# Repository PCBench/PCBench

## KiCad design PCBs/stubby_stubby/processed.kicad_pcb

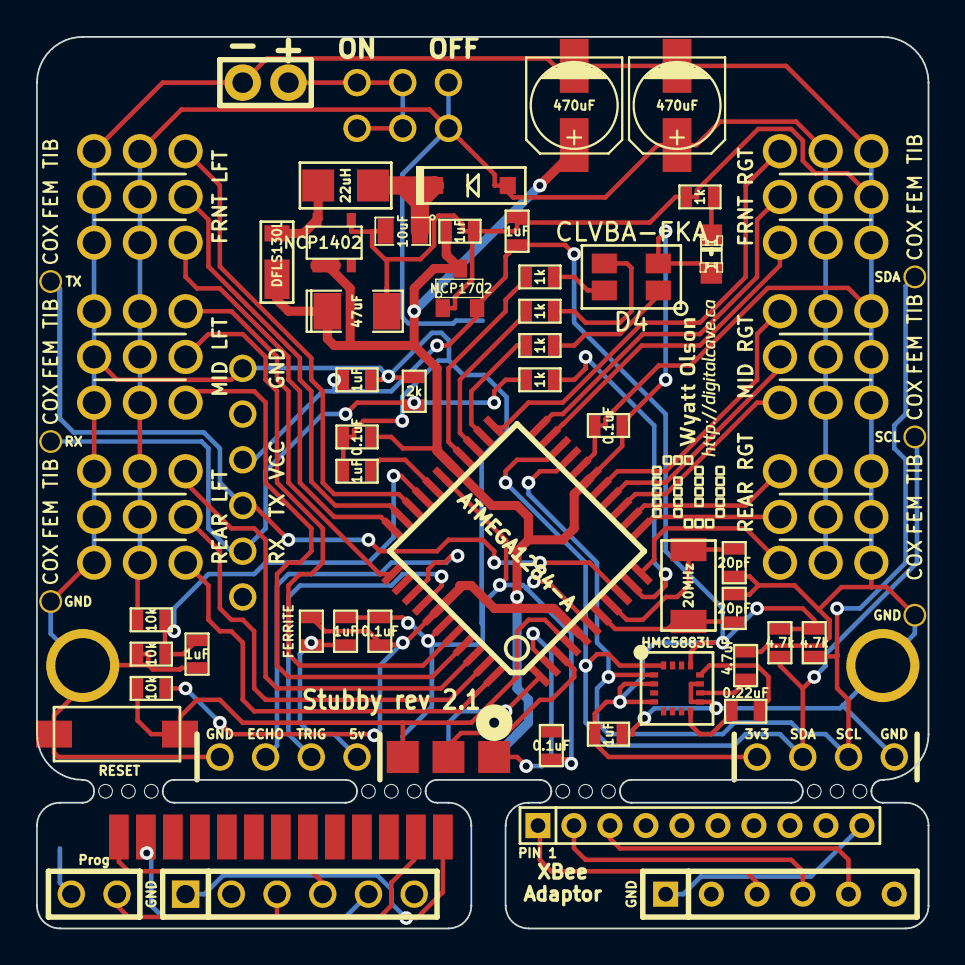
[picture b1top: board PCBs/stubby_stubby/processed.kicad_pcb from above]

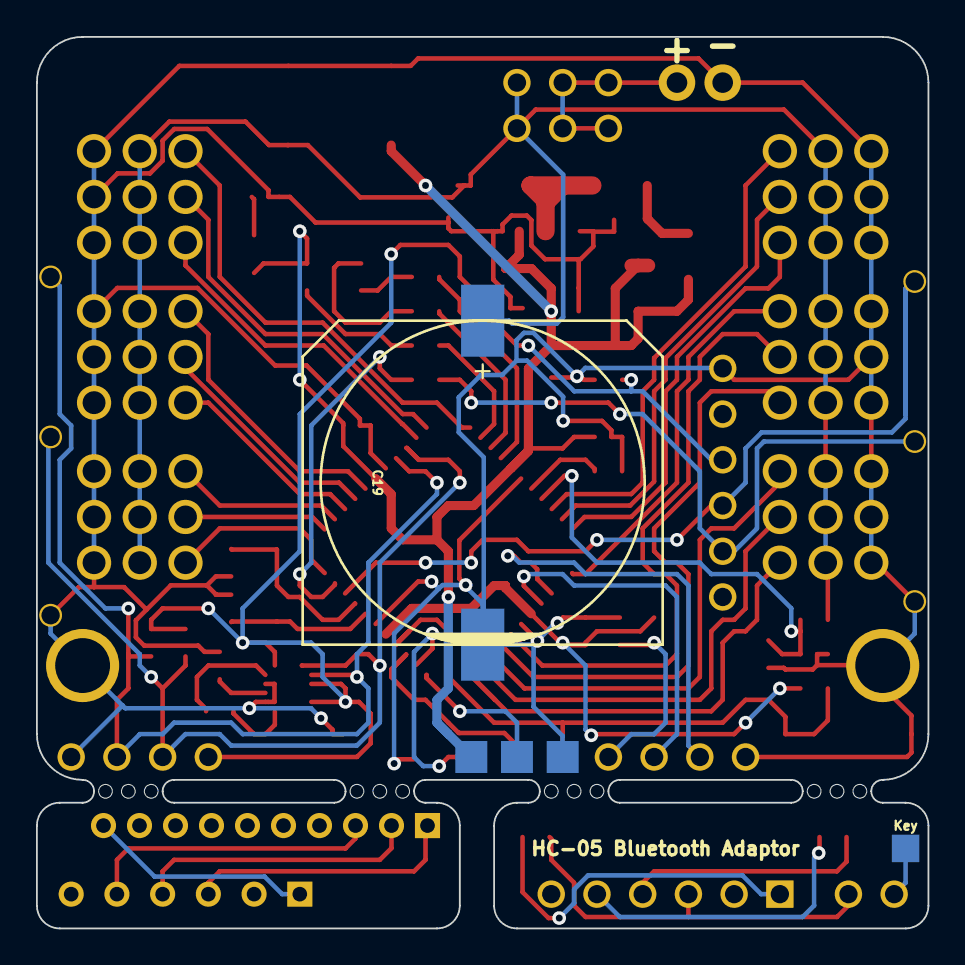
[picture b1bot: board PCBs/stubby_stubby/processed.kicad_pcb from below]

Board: 2 copper layers, 49.5 x 49.5 mm, 74 parts (2 on the bottom side), 60 nets.

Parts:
1PIN, 1PIN_2, 1PIN_3, 1PIN_4, 1PIN_5, 1PIN_6, 1PIN_7, 1PIN_8: P***; 1pin
C1: 10uF; SM0805
C2, C3, C6, C15, C16, C17, C18: 1uF; SM0603_VALUE
C4: 47uF; SM1206POL
C5, C20: 470uF; c_elec_5x5.3
C7: 4.7uF; SM0603_VALUE
C8, C9: 20pF; SM0603_VALUE
C10: 0.22uF; SM0603_VALUE
C11, C12, C13, C14: 0.1uF; SM0603_VALUE
C19: 6800µF; c_elec_18x18
D1: 1N4148W; SOD-123_DIODE
D2: DFLS130L; POWERDI_123
D3: LED; LED-0805-MARKED_ANODE
D4: CLVBA-FKA; 4-PLCC
IC1: ATMEGA1284-A; TQFP44
L1: 22uH; SM1007
L2: FERRITE; SM0603_VALUE
P1, P6, P11: CONN_6; SIL-6
P2, P10: CONN_4; SIL-4
P3: CONN_13; HC05_Edge
P4: CONN_2; SIL-2
P5: CONN_1; SIL-1
P7: CONN_10; SIL-10
P8: BATT (4.8V-6V); SIL-2
P9: PROG; ISP_EDGE
R1, R2: 4.7k; SM0603_VALUE
R3, R5, R6: 10k; SM0603_VALUE
R4, R7, R9, R10, R11: 1k; SM0603_VALUE
R8: 2k; SM0603_VALUE
S1: FRNT LFT; HEX_LEG
S2: FRNT RGT; HEX_LEG_REVERSE
S3: MID LFT; HEX_LEG
S4: MID RGT; HEX_LEG_REVERSE
S5: REAR LFT; HEX_LEG
S6: REAR RGT; HEX_LEG_REVERSE
SW1: SW_PUSH; SW_6x3
SW2: DPDT
U1: HMC5883L; LPCC-16
VAL: DIGITALCAVE_LOGO_WIDE_SMALL
VR1: MCP1702; SOT23
VR2: NCP1402; SOT23-5
X1: 20MHz; CRYSTAL_SMD_5x3.2
mouse_bites: VAL**; mouse_bites
mouse_bites_2, mouse_bites_3, mouse_bites_4: VAL**; mouse_bites

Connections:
+3.3V: C2.1, C15.1, C18.2, P2.1, P11.3, R1.2, R2.2, U1.2, U1.4, U1.13, VR1.3
+5V: C3.1, C4.1, C5.1, C11.1, C12.1, C13.1, D2.2, D3.1, D4.2, IC1.5, IC1.17, IC1.27, IC1.38, L2.2, P9.2, R3.1, VR1.2, VR2.1, VR2.2
+BATT: C19.1, C20.1, D1.1, R5.1, S1.4, S1.5, S1.6, S2.4, S2.5, S2.6, S3.4, S3.5, S3.6, S4.4, S4.5, S4.6, S5.4, S5.5, S5.6, S6.4, S6.5, S6.6, SW2.3, SW2.6
/ADC_BATTERY_METER: C16.2, IC1.30, R5.2, R6.2
/AREF: C6.2, IC1.29
/AVR_RX: 1PIN_3.1, IC1.9, P11.4
/AVR_TX: IC1.10, R7.1
/BATTERY: P8.1, SW2.1, SW2.2, SW2.4, SW2.5
/BLUETOOTH_GND: P1.1, P3.13
/DIST_ECHO: IC1.36, P10.3
/DIST_TRIG: IC1.37, P10.2
/I2C_SCL: 1PIN_6.1, IC1.19, P2.3, R1.1, U1.1
/I2C_SDA: 1PIN_7.1, IC1.20, P2.2, R2.1, U1.16
/LED_BL: IC1.25, R10.1
/LED_BL_R: D4.3, R10.2
/LED_GR: IC1.26, R9.1
/LED_GR_R: D4.4, R9.2
/LED_RD: IC1.24, R11.1
/LED_RD_R: D4.1, R11.2
/MISO: IC1.2, P9.1
/MODULE_RX: 1PIN_4.1, P11.5, R7.2, R8.2
/MOSI: IC1.1, P9.4
/PWM00: IC1.33, S1.1
/PWM01: IC1.32, S1.2
/PWM02: IC1.31, S1.3
/PWM03: IC1.23, S2.1
/PWM04: IC1.22, S2.2
/PWM05: IC1.21, S2.3
/PWM06: IC1.41, S3.1
/PWM07: IC1.40, S3.2
/PWM08: IC1.34, S3.3
/PWM09: IC1.16, S4.1
/PWM10: IC1.15, S4.2
/PWM11: IC1.14, S4.3
/PWM12: IC1.44, S5.1
/PWM13: IC1.43, S5.2
/PWM14: IC1.42, S5.3
/PWM15: IC1.13, S6.1
/PWM16: IC1.12, S6.2
/PWM17: IC1.11, S6.3
/RESET: IC1.4, P9.5, R3.2, SW1.2
/SCK: IC1.3, P9.3
/XBEE_GND: P6.1, P7.10
/XTAL1: C9.2, IC1.8, X1.1
/XTAL2: C8.2, IC1.7, X1.2
GND: 1PIN.1, 1PIN_2.1, 1PIN_5.1, 1PIN_8.1, C1.2, C2.2, C3.2, C4.2, C5.2, C6.1, C7.2, C8.1, C9.1, C11.2, C12.2, C13.2, C14.2, C15.2, C16.1, C17.2, C18.1, C19.2, C20.2, IC1.6, IC1.18, IC1.28, IC1.39, P2.4, P8.2, P9.6, P10.4, P11.1, R4.1, R6.1, R8.1, S1.7, S1.8, S1.9, S2.7, S2.8, S2.9, S3.7, S3.8, S3.9, S4.7, S4.8, S4.9, S5.7, S5.8, S5.9, S6.7, S6.8, S6.9, SW1.1, U1.9, U1.11, VR1.1, VR2.4
unnamed: C7.1, U1.10
unnamed: C10.1, U1.8
unnamed: C10.2, U1.12
unnamed: D2.1, L1.2, VR2.5
unnamed: C1.1, D1.2, L1.1
unnamed: C17.1, L2.1, P10.1
unnamed: D3.2, R4.2
unnamed: P6.3, P7.1
unnamed: P6.4, P7.2
unnamed: P6.5, P7.3
unnamed: P1.5, P3.2
unnamed: P4.1, P5.1
unnamed: P1.4, P3.1
unnamed: P1.3, P3.12, P4.2

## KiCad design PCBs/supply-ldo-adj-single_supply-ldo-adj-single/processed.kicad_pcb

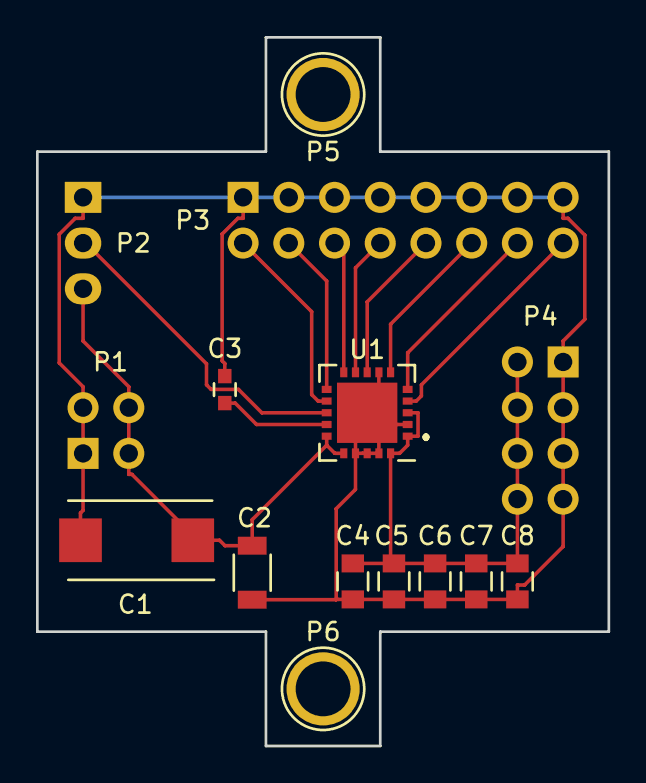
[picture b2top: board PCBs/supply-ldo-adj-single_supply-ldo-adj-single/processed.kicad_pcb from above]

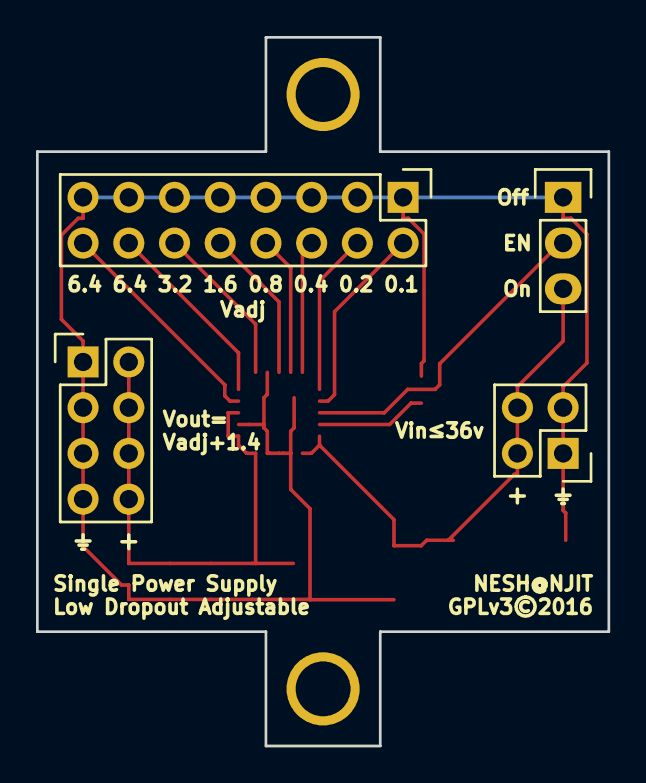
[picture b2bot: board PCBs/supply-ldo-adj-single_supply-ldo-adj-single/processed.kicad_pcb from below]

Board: 2 copper layers, 31.8 x 39.4 mm, 15 parts (4 on the bottom side), 13 nets.

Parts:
C1: T495X476K035ATE300; TantalC_SizeD_EIA-7343_Reflow
C2: UMK316BBJ106KL-T; C_1206
C3: UMK107BJ105KA-T; C_0603
C4, C5, C6, C7, C8: GRM21BR6YA106KE43L; C_0805
P1: CONN_02X02; Pin_Header_Straight_2x02
P2: CONN_01X03; Pin_Header_Straight_1x03
P3: CONN_02X08; Pin_Header_Straight_2x08
P4: CONN_02X04; Pin_Header_Straight_2x04
P5, P6: CONN_01X01; 1pin
U1: TPS7A4700RGWR; QFN-20-1EP_5x5mm_Pitch0.65mm

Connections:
/Vin: C1.1, C2.1, P1.2, P1.4, P2.3, U1.15, U1.16
/Vout: C4.1, C5.1, C6.1, C7.1, C8.1, P4.2, P4.4, P4.6, P4.8, U1.1, U1.3, U1.20
GND: C1.2, C2.2, C3.2, C4.2, C5.2, C6.2, C7.2, C8.2, P1.1, P1.3, P2.1, P3.1, P3.3, P3.5, P3.7, P3.9, P3.11, P3.13, P3.15, P4.1, P4.3, P4.5, P4.7, U1.2, U1.7, U1.17, U1.18, U1.19, U1.21
unnamed: C3.1, U1.14
unnamed: P2.2, U1.13
unnamed: P3.2, U1.12
unnamed: P3.4, U1.11
unnamed: P3.6, U1.10
unnamed: P3.8, U1.9
unnamed: P3.10, U1.8
unnamed: P3.12, U1.6
unnamed: P3.14, U1.5
unnamed: P3.16, U1.4

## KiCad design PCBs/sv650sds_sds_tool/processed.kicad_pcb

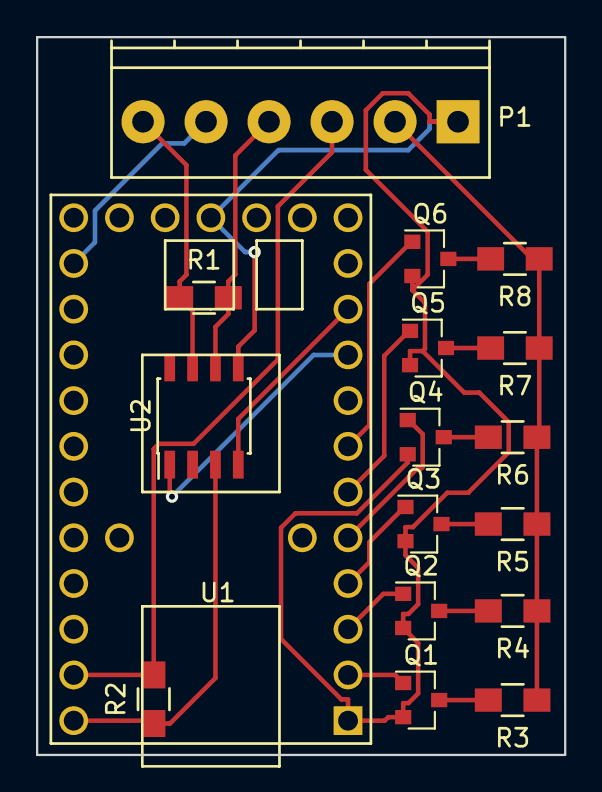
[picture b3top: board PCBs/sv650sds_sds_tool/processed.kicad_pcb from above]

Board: 2 copper layers, 29.3 x 39.9 mm, 17 parts (0 on the bottom side), 21 nets.

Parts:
P1: CONN_01X06; TerminalBlock_Pheonix_PT-3.5mm_6pol
Q1, Q2, Q3, Q4, Q5, Q6: MMBT3904; SOT-23
R1: 510; R_0805_HandSoldering
R2: 1k; R_0805_HandSoldering
R3: 560; R_0805_HandSoldering
R4: 630; R_0805_HandSoldering
R5: 1.5k; R_0805_HandSoldering
R6: 2.7k; R_0805_HandSoldering
R7: 6.8k; R_0805_HandSoldering
R8: 15k; R_0805_HandSoldering
U1: Teensy2.0
U2: STl9637; SOIC-8_3.9x4.9mm_Pitch1.27mm

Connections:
+5V: R2.1, U1.29, U2.3
+12V: P1.6, R1.1, U2.7
ECU_GPS: P1.2, R3.1, R4.1, R5.1, R6.1, R7.1, R8.1
GND: P1.1, Q1.2, Q2.2, Q3.2, Q4.2, Q5.2, Q6.2, U1.1, U1.15, U2.5
GPS: P1.3, R2.2, U1.28
Gear1: Q1.1, U1.2
Gear2: Q2.1, U1.3
Gear3: Q3.1, U1.4
Gear4: Q4.1, U1.5
Gear5: Q5.1, U1.6
Gear6: Q6.1, U1.7
K_LINE: P1.4, R1.2, U2.6
unnamed: Q1.3, R3.2
unnamed: Q2.3, R4.2
unnamed: Q3.3, R5.2
unnamed: Q4.3, R6.2
unnamed: Q5.3, R7.2
unnamed: Q6.3, R8.2
OUTPUT: P1.5, U1.19
TTL_K_RX: U1.9, U2.1
TTL_K_TX: U1.10, U2.4

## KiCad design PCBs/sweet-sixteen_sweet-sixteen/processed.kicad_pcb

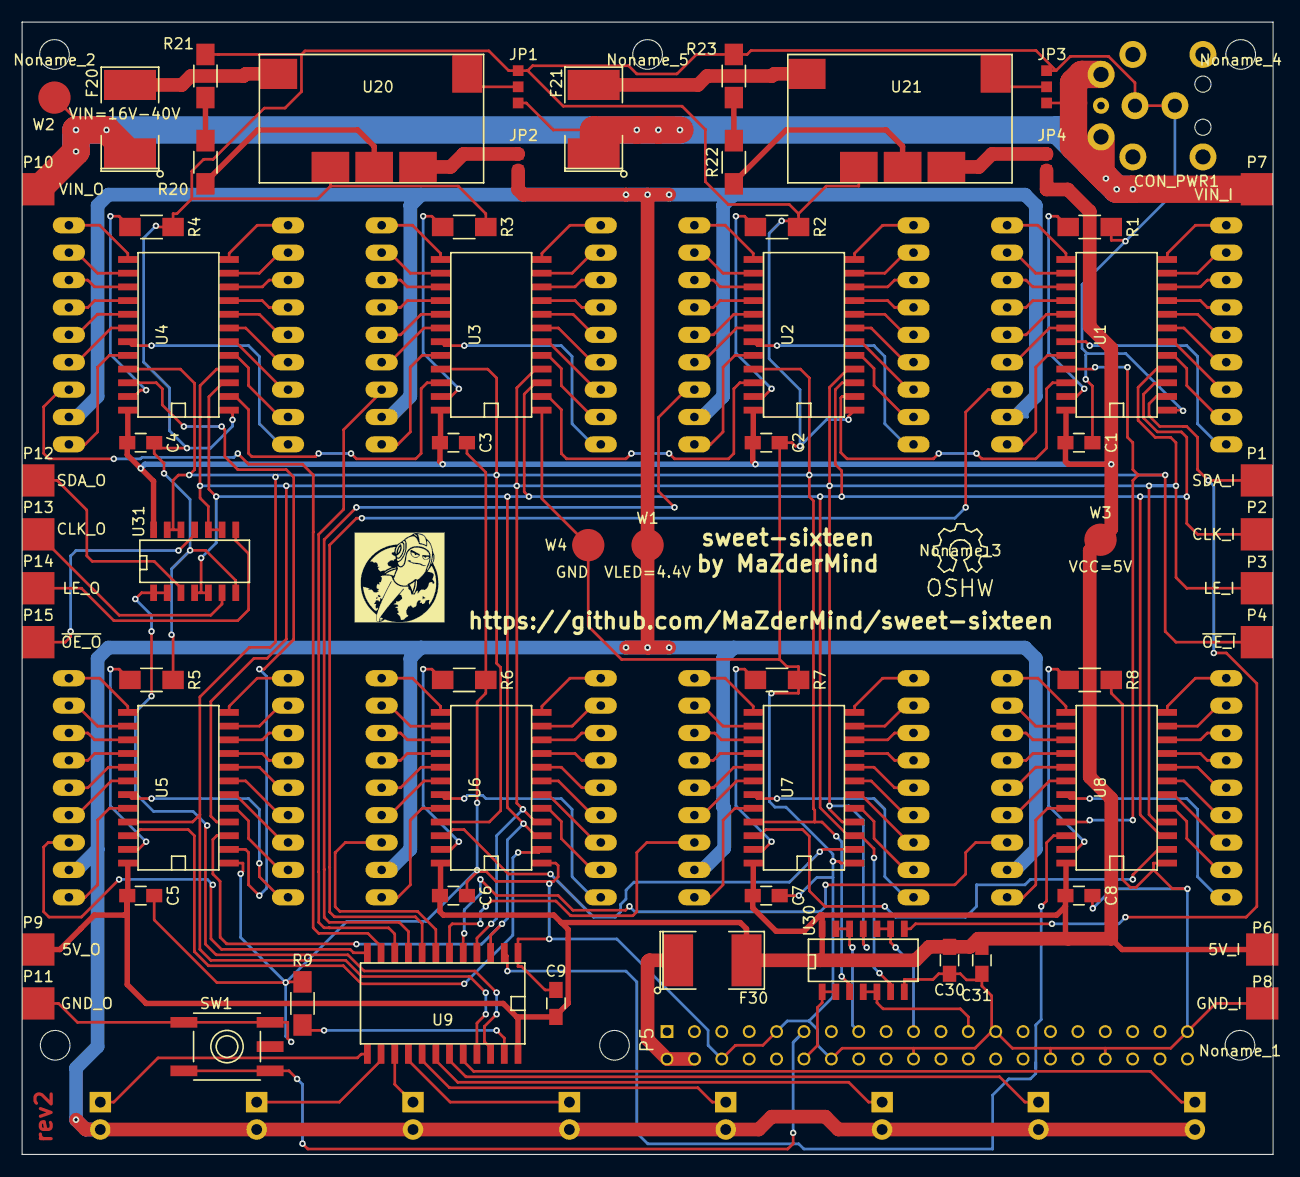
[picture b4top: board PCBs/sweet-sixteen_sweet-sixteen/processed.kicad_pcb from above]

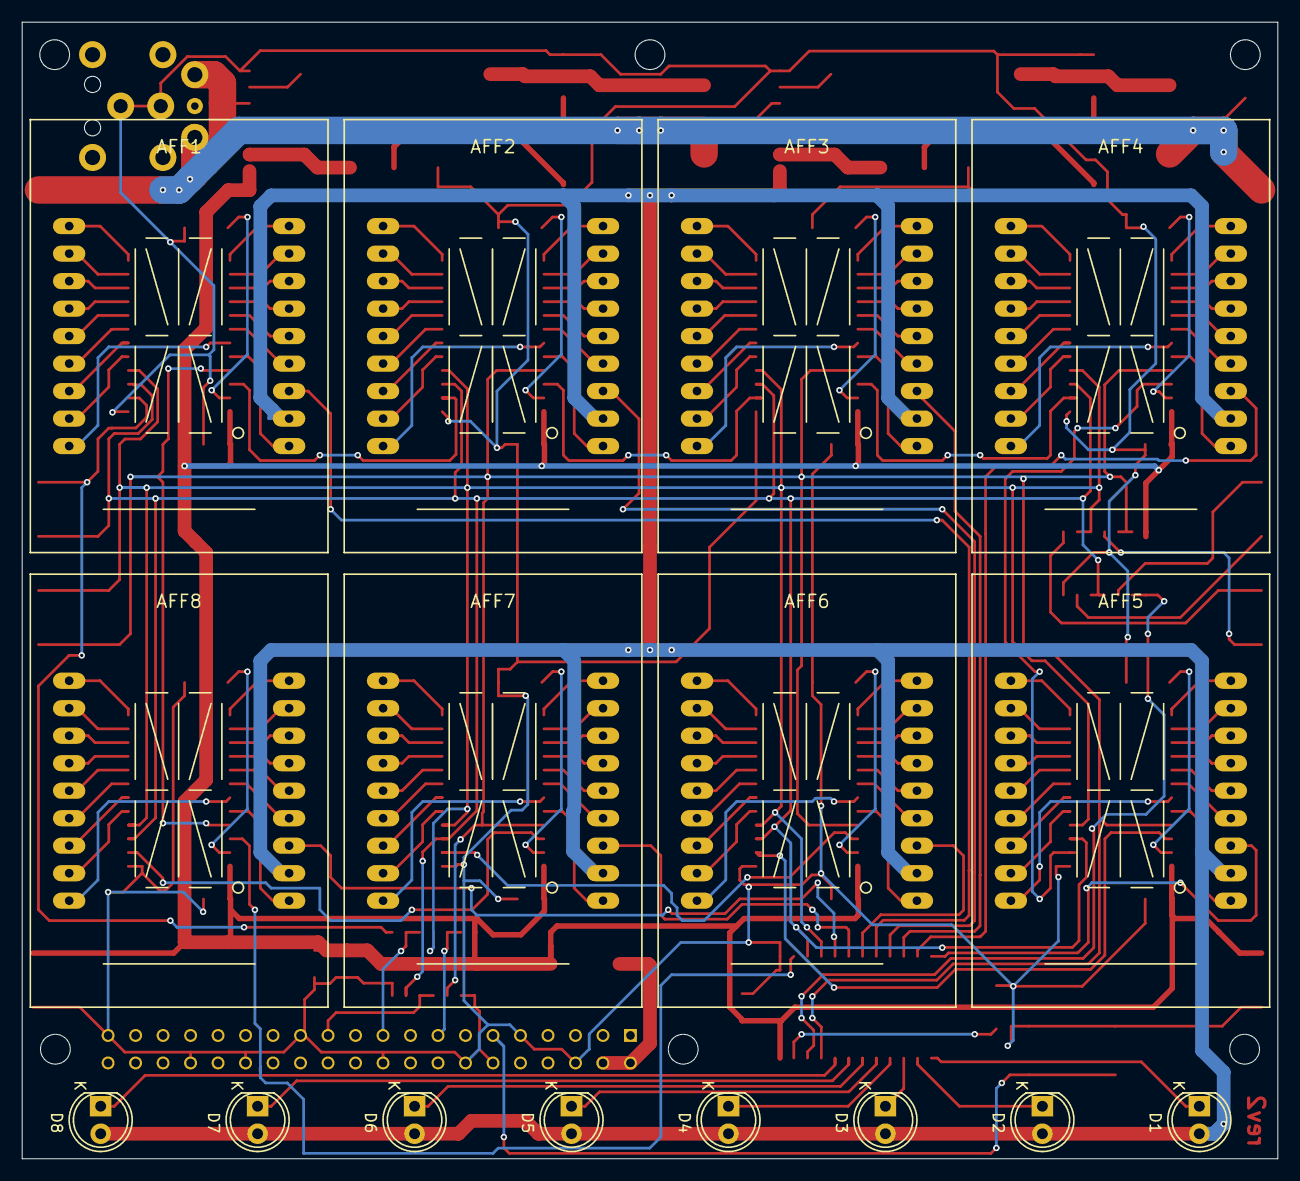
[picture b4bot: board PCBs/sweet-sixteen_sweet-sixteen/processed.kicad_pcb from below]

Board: 2 copper layers, 116.0 x 105.0 mm, 86 parts (16 on the bottom side), 190 nets.

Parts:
AFF1, AFF2, AFF3, AFF4, AFF5, AFF6, AFF7, AFF8: 16SEGMENTS; PSA12-11
C1, C2, C3, C4, C5, C6, C7, C8, C9, C30, C31: 0.1μF; C_0805_HandSoldering
CON_PWR1: PWR; DELL-PCON
D1, D2, D3, D4, D5, D6, D7, D8: LED; LED-5MM
F20, F21: 1.2A F; SMD-2112_Pol
F30: 2.5A S; SMD-2112_Pol
JP1, JP3: JUMPER3; SMD_Jumper_3
JP2, JP4: JUMPER; SMD_Jumper_2
Noname_1, Noname_2, Noname_4, Noname_5: M2.5; m25-mounting-hole
Noname_3: Symbol_OSHW-Logo_SilkScreen
P1: SDA_I; Measurement_Point_Square-SMD-Pad_Big
P2: CLK_I; Measurement_Point_Square-SMD-Pad_Big
P3: LE_I; Measurement_Point_Square-SMD-Pad_Big
P4: ~OE_I; Measurement_Point_Square-SMD-Pad_Big
P5: CONN_02X20; rpi-header
P6: 5V_I; Measurement_Point_Square-SMD-Pad_Big
P7: VIN_I; Measurement_Point_Square-SMD-Pad_Big
P8: GND_I; Measurement_Point_Square-SMD-Pad_Big
P9: 5V_O; Measurement_Point_Square-SMD-Pad_Big
P10: VIN_O; Measurement_Point_Square-SMD-Pad_Big
P11: GND_O; Measurement_Point_Square-SMD-Pad_Big
P12: SDA_O; Measurement_Point_Square-SMD-Pad_Big
P13: CLK_O; Measurement_Point_Square-SMD-Pad_Big
P14: LE_O; Measurement_Point_Square-SMD-Pad_Big
P15: ~OE_O; Measurement_Point_Square-SMD-Pad_Big
R1, R2, R3, R4, R5, R6, R7, R8, R9: 1k; R_1206_HandSoldering
R20, R22: 1.2k; R_1206_HandSoldering
R21: 680; R_1206_HandSoldering
R23: 270; R_1206_HandSoldering
SW1: SW_PUSH; ADTSM61
U1, U2, U3, U4, U5, U6, U7, U8, U9: STP16CPC26; STP16CPC26MTR
U20, U21: OKI-T/3-W40; OKI-T3
U30, U31: 74HCT08; SN74HCT08D
W1: VLED=4.4V; Measurement_Point_Round-SMD-Pad_Big
W2: VIN=16V-40V; Measurement_Point_Round-SMD-Pad_Big
W3: VCC=5V; Measurement_Point_Round-SMD-Pad_Big
W4: GND; Measurement_Point_Round-SMD-Pad_Big

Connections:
/CLK: P2.1, U1.3, U2.3, U3.3, U4.3, U5.3, U6.3, U7.3, U8.3, U9.3, U30.6, U31.4, U31.5
/CLK_O: P13.1, U31.6
/LE: P3.1, U1.4, U2.4, U3.4, U4.4, U5.4, U6.4, U7.4, U8.4, U9.4, U30.11, U31.9, U31.10
/LE_O: P14.1, U31.8
/PI_CLK: P5.23, U30.4, U30.5
/PI_LE: P5.15, U30.12, U30.13
/PI_SDA: P5.19, U30.9, U30.10
/SDA_9O: U9.22, U31.1, U31.2
/SDA_12: U1.22, U2.2
/SDA_34: U3.22, U4.2
/SDA_45: U4.22, U5.2
/SDA_56: U5.22, U6.2
/SDA_67: U6.22, U7.2
/SDA_78: U7.22, U8.2
/SDA_89: U8.22, U9.2
/SDA_I: P1.1, U1.2, U30.8
/SDA_O: P12.1, U31.3
/SD_23: U2.22, U3.2
/VLED: AFF1.11, AFF2.11, AFF3.11, AFF4.11, AFF5.11, AFF6.11, AFF7.11, AFF8.11, D1.2, D2.2, D3.2, D4.2, D5.2, D6.2, D7.2, D8.2, JP2.2, W1.1
/V_PI: F30.1, P5.2, P5.4
/~OE: P4.1, U1.21, U2.21, U3.21, U4.21, U5.21, U6.21, U7.21, U8.21, U9.21, U30.3, U31.12, U31.13
/~OE_O: P15.1, U31.11
/~PI_OE: P5.12, U30.1, U30.2
GND: C1.2, C2.2, C3.2, C4.2, C5.2, C6.2, C7.2, C8.2, C9.2, C30.2, C31.2, CON_PWR1.2, JP1.1, JP3.1, P5.6, P5.9, P5.14, P5.20, P5.25, P5.30, P5.34, P5.39, P8.1, P11.1, R1.1, R2.1, R3.1, R4.1, R5.1, R6.1, R7.1, R8.1, R9.1, R21.2, R23.2, SW1.1, U1.1, U2.1, U3.1, U4.1, U5.1, U6.1, U7.1, U8.1, U9.1, U20.3, U21.3, U30.7, U31.7, W4.1
unnamed: AFF1.1, U1.12
unnamed: AFF1.2, U1.11
unnamed: AFF1.3, U1.10
unnamed: AFF1.4, U1.9
unnamed: AFF1.5, U1.8
unnamed: AFF1.6, U1.7
unnamed: AFF1.7, U1.6
unnamed: AFF1.8, U1.5
unnamed: AFF1.9, U1.19
unnamed: AFF1.10, U1.20
unnamed: AFF1.12, U9.8
unnamed: AFF1.13, U1.18
unnamed: AFF1.14, U1.17
unnamed: AFF1.15, U1.16
unnamed: AFF1.16, U1.15
unnamed: AFF1.17, U1.14
unnamed: AFF1.18, U1.13
unnamed: AFF2.1, U2.12
unnamed: AFF2.2, U2.11
unnamed: AFF2.3, U2.10
unnamed: AFF2.4, U2.9
unnamed: AFF2.5, U2.8
unnamed: AFF2.6, U2.7
unnamed: AFF2.7, U2.6
unnamed: AFF2.8, U2.5
unnamed: AFF2.9, U2.19
unnamed: AFF2.10, U2.20
unnamed: AFF2.12, U9.9
unnamed: AFF2.13, U2.18
unnamed: AFF2.14, U2.17
unnamed: AFF2.15, U2.16
unnamed: AFF2.16, U2.15
unnamed: AFF2.17, U2.14
unnamed: AFF2.18, U2.13
unnamed: AFF3.1, U3.12
unnamed: AFF3.2, U3.11
unnamed: AFF3.3, U3.10
unnamed: AFF3.4, U3.9
unnamed: AFF3.5, U3.8
unnamed: AFF3.6, U3.7
unnamed: AFF3.7, U3.6
unnamed: AFF3.8, U3.5
unnamed: AFF3.9, U3.19
unnamed: AFF3.10, U3.20
unnamed: AFF3.12, U9.10
unnamed: AFF3.13, U3.18
unnamed: AFF3.14, U3.17
unnamed: AFF3.15, U3.16
unnamed: AFF3.16, U3.15
unnamed: AFF3.17, U3.14
unnamed: AFF3.18, U3.13
unnamed: AFF4.1, U4.12
unnamed: AFF4.2, U4.11
unnamed: AFF4.3, U4.10
unnamed: AFF4.4, U4.9
unnamed: AFF4.5, U4.8
unnamed: AFF4.6, U4.7
unnamed: AFF4.7, U4.6
unnamed: AFF4.8, U4.5
unnamed: AFF4.9, U4.19
unnamed: AFF4.10, U4.20
unnamed: AFF4.12, U9.11
unnamed: AFF4.13, U4.18
unnamed: AFF4.14, U4.17
unnamed: AFF4.15, U4.16
unnamed: AFF4.16, U4.15
unnamed: AFF4.17, U4.14
unnamed: AFF4.18, U4.13
unnamed: AFF5.1, U5.12
unnamed: AFF5.2, U5.11
unnamed: AFF5.3, U5.10
unnamed: AFF5.4, U5.9
unnamed: AFF5.5, U5.8
unnamed: AFF5.6, U5.7
unnamed: AFF5.7, U5.6
unnamed: AFF5.8, U5.5
unnamed: AFF5.9, U5.19
unnamed: AFF5.10, U5.20
unnamed: AFF5.12, U9.12
unnamed: AFF5.13, U5.18
unnamed: AFF5.14, U5.17
unnamed: AFF5.15, U5.16
unnamed: AFF5.16, U5.15
unnamed: AFF5.17, U5.14
unnamed: AFF5.18, U5.13
unnamed: AFF6.1, U6.12
unnamed: AFF6.2, U6.11
unnamed: AFF6.3, U6.10
unnamed: AFF6.4, U6.9
unnamed: AFF6.5, U6.8
unnamed: AFF6.6, U6.7
unnamed: AFF6.7, U6.6
unnamed: AFF6.8, U6.5
unnamed: AFF6.9, U6.19
unnamed: AFF6.10, U6.20
unnamed: AFF6.12, U9.7
unnamed: AFF6.13, U6.18
unnamed: AFF6.14, U6.17
unnamed: AFF6.15, U6.16
unnamed: AFF6.16, U6.15
unnamed: AFF6.17, U6.14
unnamed: AFF6.18, U6.13
unnamed: AFF7.1, U7.12
unnamed: AFF7.2, U7.11
unnamed: AFF7.3, U7.10
unnamed: AFF7.4, U7.9
unnamed: AFF7.5, U7.8
unnamed: AFF7.6, U7.7
unnamed: AFF7.7, U7.6
unnamed: AFF7.8, U7.5
unnamed: AFF7.9, U7.19
unnamed: AFF7.10, U7.20
unnamed: AFF7.12, U9.6
unnamed: AFF7.13, U7.18
unnamed: AFF7.14, U7.17
unnamed: AFF7.15, U7.16
unnamed: AFF7.16, U7.15
unnamed: AFF7.17, U7.14
unnamed: AFF7.18, U7.13
unnamed: AFF8.1, U8.12
unnamed: AFF8.2, U8.11
unnamed: AFF8.3, U8.10
unnamed: AFF8.4, U8.9
unnamed: AFF8.5, U8.8
unnamed: AFF8.6, U8.7
unnamed: AFF8.7, U8.6
unnamed: AFF8.8, U8.5
unnamed: AFF8.9, U8.19
unnamed: AFF8.10, U8.20
unnamed: AFF8.12, U9.5
unnamed: AFF8.13, U8.18
unnamed: AFF8.14, U8.17
unnamed: AFF8.15, U8.16
unnamed: AFF8.16, U8.15
unnamed: AFF8.17, U8.14
unnamed: AFF8.18, U8.13
unnamed: D1.1, U9.13
unnamed: D2.1, U9.14
unnamed: D3.1, U9.15
unnamed: D4.1, U9.16
unnamed: D5.1, U9.17
unnamed: D6.1, U9.18
unnamed: D7.1, U9.19
unnamed: D8.1, U9.20
unnamed: F20.2, U20.2
unnamed: F21.2, U21.2
unnamed: JP1.2, U20.1
unnamed: JP2.1, U20.5
unnamed: JP3.2, U21.1
unnamed: JP4.1, U21.5
unnamed: P5.11, SW1.2
unnamed: R1.2, U1.23
unnamed: R2.2, U2.23
unnamed: R3.2, U3.23
unnamed: R4.2, U4.23
unnamed: R5.2, U5.23
unnamed: R6.2, U6.23
unnamed: R7.2, U7.23
unnamed: R8.2, U8.23
unnamed: R9.2, U9.23
unnamed: R20.1, R21.1
unnamed: R20.2, U20.4
unnamed: R22.1, R23.1
unnamed: R22.2, U21.4
VCC: C1.1, C2.1, C3.1, C4.1, C5.1, C6.1, C7.1, C8.1, C9.1, C30.1, C31.1, F30.2, JP4.2, P6.1, P9.1, U1.24, U2.24, U3.24, U4.24, U5.24, U6.24, U7.24, U8.24, U9.24, U30.14, U31.14, W3.1
VIN: CON_PWR1.1, F20.1, F21.1, JP1.3, JP3.3, P7.1, P10.1, W2.1

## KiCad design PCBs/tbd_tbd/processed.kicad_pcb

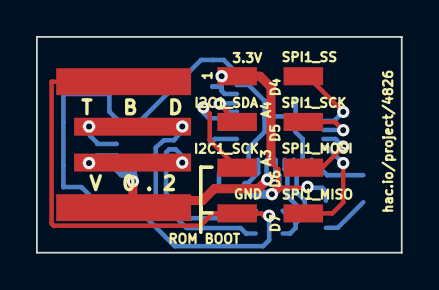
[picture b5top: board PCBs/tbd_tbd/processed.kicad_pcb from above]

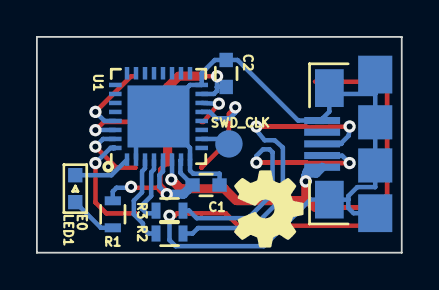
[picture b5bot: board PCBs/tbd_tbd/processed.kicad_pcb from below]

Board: 2 copper layers, 20.3 x 12.0 mm, 11 parts (9 on the bottom side), 16 nets.

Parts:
C1, C2: 100nF; C_0603
J1: USBPCB; tbd_USB_A_PCB
J2: USB-MICROB-5PIN; SparkFun-USB-MICROB
LED1: LED0603; LED-0603
P1: CONN_02X04; HEADER_2x4_SMT_RA
R1: 100R; R_0603
R2, R3: 33R; R_0603
SWD_CLK: SWD_CLK; Measurement_Point_Round-SMD-Pad_Small
U1: MKL27ZxxxVFM4; QFN-32-1EP_5x5mm_Pitch0.5mm

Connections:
+3.3V: C1.1, C2.1, P1.1, R1.1, U1.5, U1.7, U1.15
I2C1_SCL: P1.5, U1.13
I2C1_SDA: P1.3, U1.14
unnamed: J1.5V, J2.VBUS, U1.6
unnamed: J1.DN, J2.D-, R3.1
unnamed: J1.DP, J2.D+, R2.1
unnamed: LED1.A, R1.2
unnamed: LED1.C, U1.1
unnamed: R2.2, U1.3
unnamed: R3.2, U1.4
unnamed: SWD_CLK.1, U1.10
SPI1_MISO: P1.8, U1.32
SPI1_MOSI: P1.6, U1.31
SPI1_SCK: P1.4, U1.30
SPI1_SS: P1.2, U1.29
VSS: C1.2, C2.2, J1.GND, J2.GND, J2.MTN1, J2.MTN2, J2.MTN3, J2.MTN4, J2.MTN5, J2.MTN6, P1.7, U1.2, U1.8, U1.16, U1.33

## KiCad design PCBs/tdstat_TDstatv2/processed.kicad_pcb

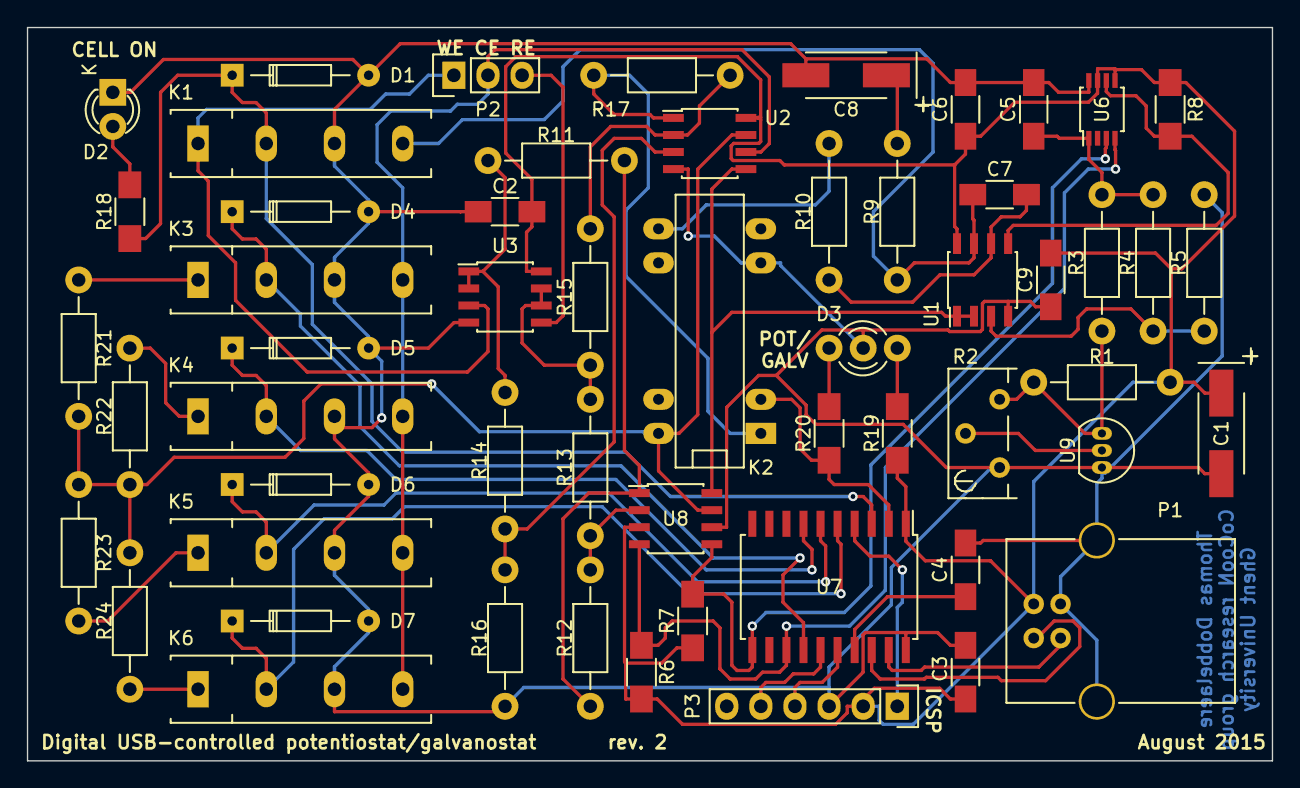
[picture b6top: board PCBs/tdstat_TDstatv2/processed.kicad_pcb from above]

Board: 2 copper layers, 92.7 x 54.6 mm, 56 parts (0 on the bottom side), 44 nets.

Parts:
C1, C8: 10 µF; TantalC_SizeC_EIA-6032_HandSoldering
C2, C3, C4, C5, C6, C7, C9: 0.1 µF; C_1206_HandSoldering
D1, D4, D5, D6, D7: 1N4148; Diode_DO-35_SOD27_Horizontal_RM10
D2: CELL ON LED; LED-3MM
D3: MODE LED; DUO-LED-3mm
K1, K3, K4, K5, K6: 9007-05-00; RELAY-9007
K2: HE721C0510; RELAY-HE700
P1: USB_B
P2: CELL_CONN; Pin_Header_Straight_1x03
P3: ICSP_CONN; Pin_Header_Straight_1x06
R1: 1k; Resistor_Horizontal_RM10mm
R2: 10k; Potentiometer_Bourns_3296Y_3-8Zoll_Angular_ScrewUp
R3, R23: 10k 0.1%; Resistor_Horizontal_RM10mm
R4: 18k 0.1%; Resistor_Horizontal_RM10mm
R5: 2k 0.1%; Resistor_Horizontal_RM10mm
R6, R7: 4k7; R_1206_HandSoldering
R8: 100k; R_1206_HandSoldering
R9: 27; Resistor_Horizontal_RM10mm
R10: 100k; Resistor_Horizontal_RM10mm
R11, R12, R13, R22: 1k 0.1%; Resistor_Horizontal_RM10mm
R14, R15: 200k 0.1%; Resistor_Horizontal_RM10mm
R16, R17, R24: 100k 0.1%; Resistor_Horizontal_RM10mm
R18, R19, R20: 1k; R_1206_HandSoldering
R21: 100R 0.1%; Resistor_Horizontal_RM10mm
U1, U2, U3: AD8629; SOIC-8_3.9x4.9mm_Pitch1.27mm
U6: MAX5217; TSSOP-8_3x3mm_Pitch0.65mm
U7: PIC16F1459; SOIC-20_7.5x12.8mm_Pitch1.27mm
U8: MCP3422; SOIC-8_3.9x4.9mm_Pitch1.27mm
U9: TL431; TO-92_Inline_Narrow_Oval

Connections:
+5V: C1.1, C2.1, C3.1, C6.1, C9.1, P1.1, P3.2, R1.2, R6.1, R7.1, R8.2, R19.2, U1.8, U2.8, U3.8, U6.5, U6.7, U7.1, U8.3
/CE: K3.4, K4.4, K5.4, K6.4, P2.2, U2.6
/CELL_ON: D1.1, K1.2, R18.2, U7.3
/D+: P1.3, U7.19
/D-: P1.2, U7.18
/GALV_SENSE+: U1.1, U1.2, U2.5, U8.8
/GALV_SENSE-: K2.14, R21.2, R22.2, R23.2, R24.2, U2.7, U8.7
/ICSPCLK: P3.5, U7.15
/ICSPDAT: P3.4, U7.16
/MCLR: P3.1, U7.4
/MODE_SW: K2.2, R20.2, U7.2
/RANGE1: D4.1, K3.2, U7.14
/RANGE2: D5.1, K4.2, U7.7
/RANGE3: D6.1, K5.2, U7.6
/RANGE4: D7.1, K6.2, U7.5
/RE: P2.3, U3.5
/SCL: R7.2, U6.3, U7.11, U8.5
/SDA: R6.2, U6.4, U7.13, U8.4
/V_REF_2.4V: C5.2, R3.2, R4.2, U6.1
/WE: K1.1, P2.1, U3.3
GND: C1.2, C2.2, C3.2, C4.1, C5.1, C6.2, C8.2, C9.2, D1.2, D2.1, D3.2, D4.2, D5.2, D6.2, D7.2, K1.3, K2.6, K3.3, K4.3, K5.3, K6.3, P1.4, P1.5, P3.3, R2.1, R5.1, R16.2, U1.4, U2.4, U3.4, U6.8, U7.20, U8.6, U9.3
unnamed: C4.2, U7.17
unnamed: C7.1, K1.4, R9.1, U1.7
unnamed: C7.2, R10.2, U1.6
unnamed: C8.1, R9.2
unnamed: D2.2, R18.1
unnamed: D3.1, R19.1
unnamed: D3.3, R20.1
unnamed: K2.1, R17.2, U2.1
unnamed: K2.8, R10.1
unnamed: K3.1, R21.1
unnamed: K4.1, R22.1
unnamed: K5.1, R23.1
unnamed: K6.1, R24.1
unnamed: R1.1, R2.3, R3.1, U9.1
unnamed: R2.2, U9.2
unnamed: R4.1, R5.2, U1.3
unnamed: R8.1, U1.5, U6.6
unnamed: R11.1, R12.2, U8.1
unnamed: R11.2, R14.2, U3.1, U3.2
unnamed: R12.1, R13.2, U8.2
unnamed: R13.1, R15.1, U3.6, U3.7
unnamed: R14.1, R16.1, U2.3
unnamed: R15.2, R17.1, U2.2

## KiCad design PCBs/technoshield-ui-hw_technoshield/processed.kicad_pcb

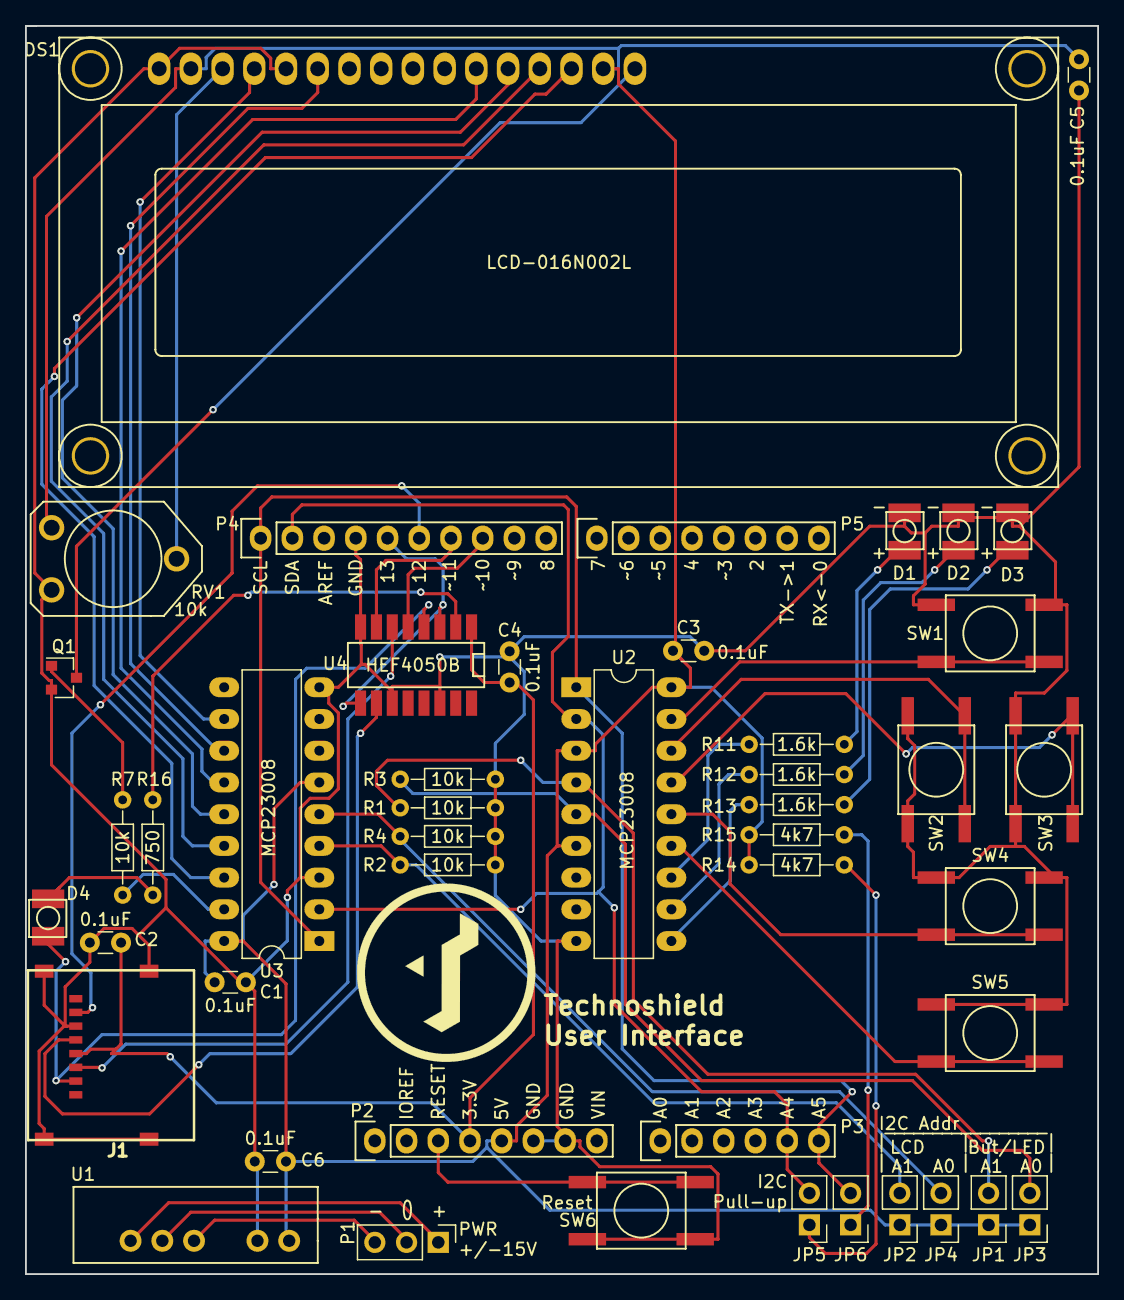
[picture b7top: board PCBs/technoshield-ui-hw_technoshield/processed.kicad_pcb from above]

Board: 2 copper layers, 85.9 x 99.9 mm, 46 parts (0 on the bottom side), 45 nets.

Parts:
C1, C2, C3, C4, C5, C6: 0.1uF; C_Disc_D3.0mm_W1.6mm_P2.50mm
D1: LS T67K-J1K2-1-Z; T67K
D2: LY T67K-J2L1-26-Z; T67K
D3, D4: LP T67K-E1F2-25-Z; T67K
DS1: LCD-016N002L; WC1602A
J1: 101-00303-68-1-ND; MICRO_SD_HINGE_AMP
JP1, JP2, JP3, JP4, JP5, JP6: JUMPER; Pin_Header_Straight_1x02_Pitch2.54mm
P1: CONN_01X03; Pin_Header_Straight_1x03_Pitch2.54mm
P2: Power; Socket_Strip_Arduino_1x08
P3: Analog; Socket_Strip_Arduino_1x06
P4: Digital; Socket_Strip_Arduino_1x10
P5: Digital; Socket_Strip_Arduino_1x08
Q1: MMBT2222A-7-F; SOT-23
R1, R2, R3, R4, R7: 10k; R_Axial_DIN0204_L3.6mm_D1.6mm_P7.62mm_Horizontal
R11, R12, R13: 1.6k; R_Axial_DIN0204_L3.6mm_D1.6mm_P7.62mm_Horizontal
R14, R15: 4k7; R_Axial_DIN0204_L3.6mm_D1.6mm_P7.62mm_Horizontal
R16: 750; R_Axial_DIN0204_L3.6mm_D1.6mm_P7.62mm_Horizontal
RV1: 10k; POTENTIOMETRE_BOURNS_3319P
SW1, SW2, SW3, SW4, SW5, SW6: SW_PUSH; smt_btn
U1: PDM1-S5-D15-S; PDM1-S
U2, U3: MCP23008; DIP-18_W7.62mm_LongPads
U4: HEF4050B; SO16-3_9mm

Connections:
+3V3: C2.1, C4.1, J1.4, P2.4, U4.1
+5V: C1.1, C3.1, C5.1, C6.1, DS1.2, DS1.15, JP1.1, JP2.1, JP3.1, JP4.1, P2.5, R14.1, R15.1, RV1.1, U1.1, U2.3, U2.6, U2.18, U3.6, U3.18
/10(**/SS): P4.8, U4.5
/11(**/MOSI): P4.7, U4.7
/12(MISO): J1.7, P4.6
/13(SCK): P4.5, U4.3, U4.9
/A4(SDA): JP5.2, P3.5, P4.2, U2.2, U3.2
/A5(SCL): JP6.2, P3.6, P4.1, U2.1, U3.1
/Reset: P2.3, SW6.2
GND: C1.2, C2.2, C3.2, C4.2, C5.2, C6.2, D1.1, D2.1, D3.1, DS1.1, DS1.5, J1.6, J1.SHLD, P2.6, P2.7, P4.4, Q1.2, R1.2, R2.2, R3.2, R4.2, RV1.3, SW1.2, SW2.2, SW3.2, SW4.2, SW5.2, SW6.1, U1.2, U2.9, U3.3, U3.9, U4.8, U4.11, U4.14
unnamed: D1.2, R11.1
unnamed: D2.2, R12.1
unnamed: D3.2, R13.1
unnamed: D4.1, J1.2, U4.4
unnamed: D4.2, R16.1
unnamed: DS1.3, RV1.2
unnamed: DS1.4, U3.11
unnamed: DS1.6, U3.12
unnamed: DS1.11, U3.13
unnamed: DS1.12, U3.14
unnamed: DS1.13, U3.15
unnamed: DS1.14, U3.16
unnamed: DS1.16, Q1.3
unnamed: J1.3, U4.6
unnamed: J1.5, U4.10
unnamed: JP1.2, R1.1, U2.4
unnamed: JP2.2, R2.1, U3.4
unnamed: JP3.2, R3.1, U2.5
unnamed: JP4.2, R4.1, U3.5
unnamed: JP5.1, R14.2
unnamed: JP6.1, R15.2
unnamed: P1.1, U1.6
unnamed: P1.2, U1.5
unnamed: P1.3, U1.4
unnamed: Q1.1, R7.1
unnamed: R7.2, U3.17
unnamed: R11.2, U2.12
unnamed: R12.2, U2.11
unnamed: R13.2, U2.10
unnamed: R16.2, U4.2
unnamed: SW1.1, U2.17
unnamed: SW2.1, U2.16
unnamed: SW3.1, U2.15
unnamed: SW4.1, U2.14
unnamed: SW5.1, U2.13

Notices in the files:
PCBs/supply-ldo-adj-single_supply-ldo-adj-single/processed.kicad_pcb:
GPLv3©2016
PCBs/technoshield-ui-hw_technoshield/processed.kicad_pcb:
Released under the Creative Commons Attribution Share-Alike 4.0 License
Copyright 2017 Jean-Sébastien Castonguay
